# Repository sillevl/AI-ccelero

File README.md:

# AI-ccelero

Small battery powered circuit with accelerometer and LoRaWAN for AI projects.

* 27x30mm
* STM32L432KC
* LSM6DSM (Accelerometer + gyroscope)
* LSM303AGR (Magnetometer + Accelerometer)
* RFM95W (LoRaWAN)
* CR2450 Battery (540mAh)
* Chip antenna
* USB connector for DFU

## Example sketches

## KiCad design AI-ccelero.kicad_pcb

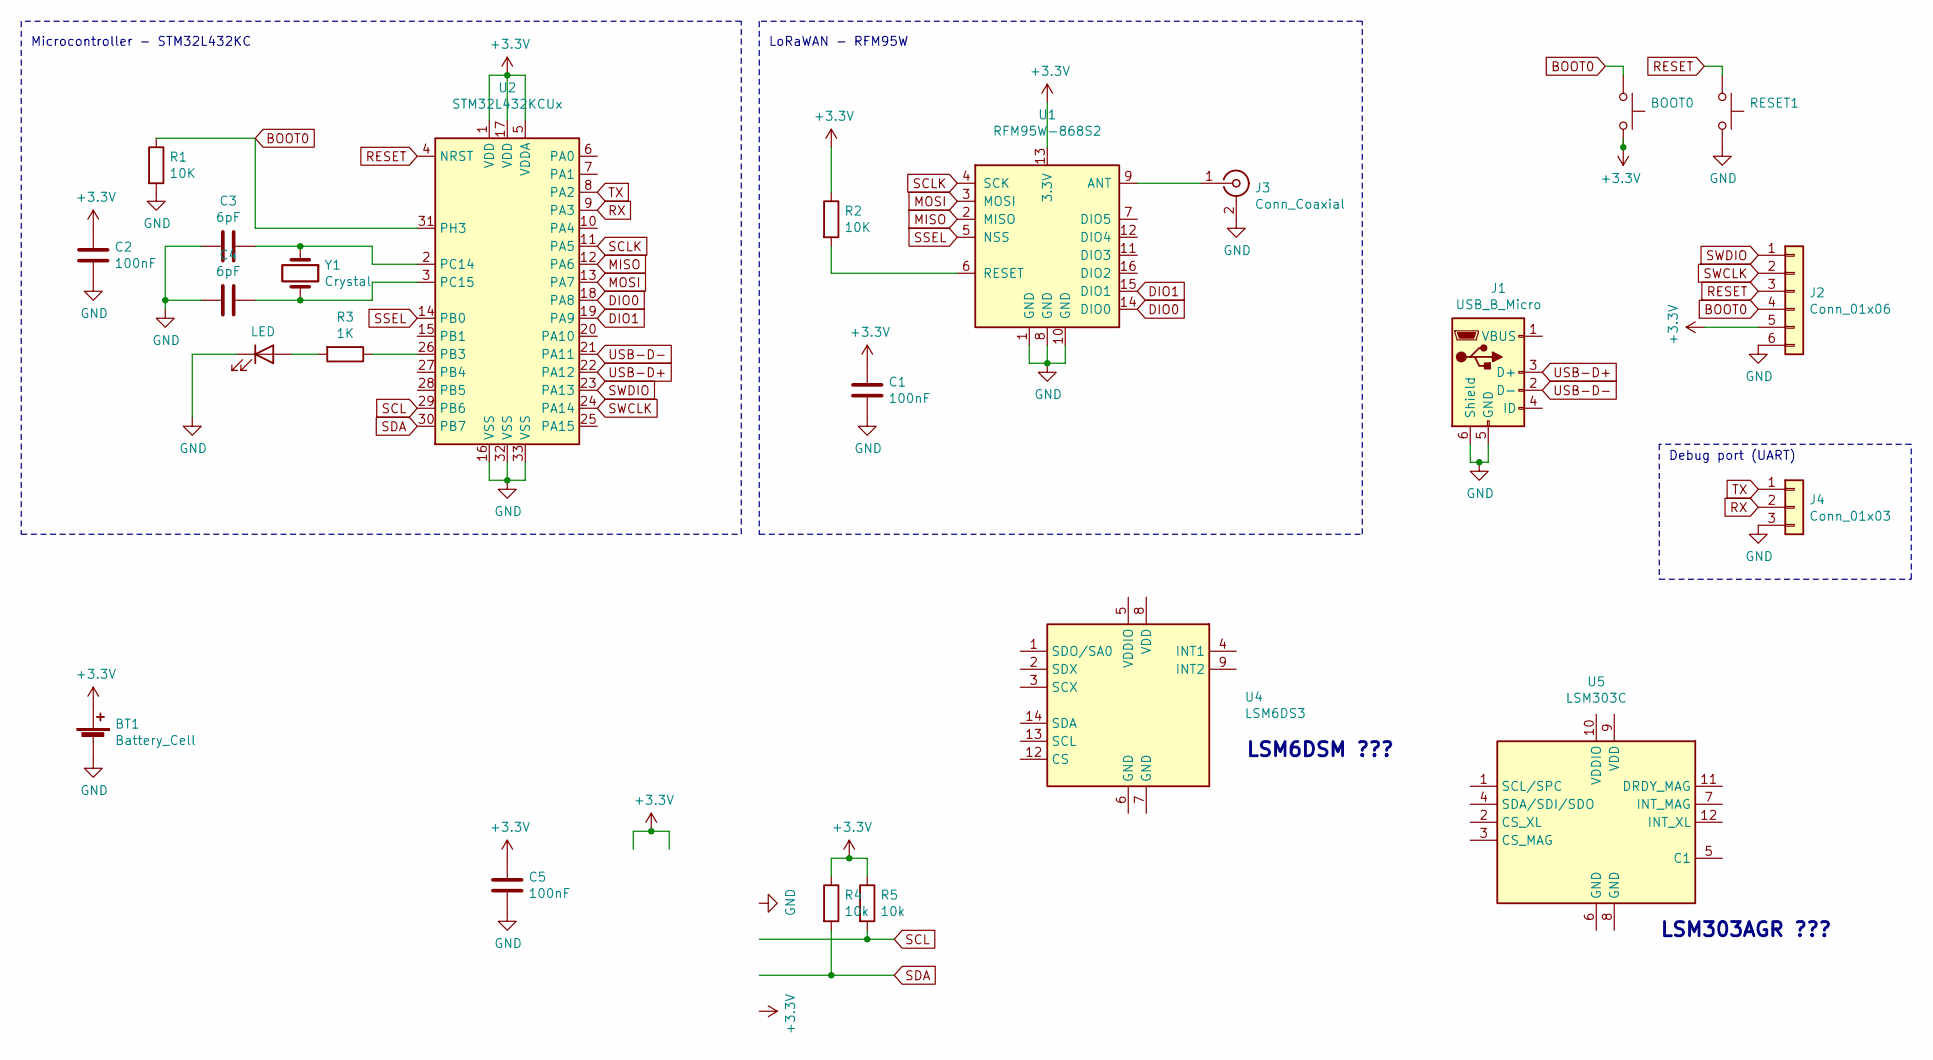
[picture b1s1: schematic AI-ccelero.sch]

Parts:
BOOT0: BOOT0; SW_SPST_B3U-1000P
BT1: Battery_Cell; BatteryHolder_Keystone_3009_1x2450
C1, C2, C5: 100nF; C_0603_1608Metric_Pad1.05x0.95mm_HandSolder
C3, C4: 6pF; C_0603_1608Metric_Pad1.05x0.95mm_HandSolder
J1: USB_B_Micro; USB_Micro-AB_Molex_47590-0001
J2: Conn_01x06; PinHeader_1x06_P2.54mm_Vertical
J3: Conn_Coaxial; Johanson_2450AT43F0100
J4: Conn_01x03; PinHeader_1x03_P2.54mm_Vertical
LED1: LED; LED_0603_1608Metric_Pad1.05x0.95mm_HandSolder
R1, R2: 10K; C_0603_1608Metric_Pad1.05x0.95mm_HandSolder
R3: 1K; C_0603_1608Metric_Pad1.05x0.95mm_HandSolder
R4, R5: 10k; C_0603_1608Metric_Pad1.05x0.95mm_HandSolder
RESET1: RESET; SW_SPST_B3U-1000P
U1: RFM95W-868S2; HOPERF_RFM9XW_SMD
U2: STM32L432KCUx; QFN-32-1EP_5x5mm_P0.5mm_EP3.45x3.45mm
U4: LSM6DS3; LGA-14_3x2.5mm_P0.5mm_LayoutBorder3x4y
U5: LSM303C; LGA-12_2x2mm_P0.5mm
Y1: Crystal; Crystal_SMD_Abracon_ABM7-2Pin_6.0x3.5mm

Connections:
+3V3: BOOT0.2, BT1.1 (+), C1.1, C2.1, C5.1, J2.5, R2.1, R4.1, R5.1, U1.13 (3.3V), U2.1 (VDD), U2.5 (VDDA), U2.17 (VDD)
BOOT0: BOOT0.1, J2.4, R1.1, U2.31 (PH3)
DIO0: U1.14 (DIO0), U2.18 (PA8)
DIO1: U1.15 (DIO1), U2.19 (PA9)
GND: BT1.2 (-), C1.2, C2.2, C3.2, C4.2, C5.2, J1.5 (GND), J1.6 (Shield), J2.6, J3.2 (Ext), J4.3, LED1.1 (K), R1.2, RESET1.2, U1.1 (GND), U1.8 (GND), U1.10 (GND), U2.16 (VSS), U2.32 (VSS), U2.33 (VSS)
MISO: U1.2 (MISO), U2.12 (PA6)
MOSI: U1.3 (MOSI), U2.13 (PA7)
unnamed: C3.1, U2.2 (PC14), Y1.1
unnamed: C4.1, U2.3 (PC15), Y1.2
unnamed: J3.1 (In), U1.9 (ANT)
unnamed: LED1.2 (A), R3.2
unnamed: R2.2, U1.6 (RESET)
unnamed: R3.1, U2.26 (PB3)
RESET: J2.3, RESET1.1, U2.4 (NRST)
RX: J4.2, U2.9 (PA3)
SCL: R5.2, U2.29 (PB6)
SCLK: U1.4 (SCK), U2.11 (PA5)
SDA: R4.2, U2.30 (PB7)
SSEL: U1.5 (NSS), U2.14 (PB0)
SWCLK: J2.2, U2.24 (PA14)
SWDIO: J2.1, U2.23 (PA13)
TX: J4.1, U2.8 (PA2)
USB-D+: J1.3 (D+), U2.22 (PA12)
USB-D-: J1.2 (D-), U2.21 (PA11)

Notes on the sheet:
Debug port (UART)
Microcontroller - STM32L432KC
LoRaWAN - RFM95W
LSM6DSM ???
LSM303AGR ???

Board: 2 copper layers, 23 parts (1 on the bottom side), 24 nets, no tracks yet.

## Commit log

2020-10-12 first sketch
